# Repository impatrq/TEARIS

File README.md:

# TEARIS 🚀

**Auriculares con cancelación selectiva de ruido para personas con TEA y sensibilidad auditiva**

---

## 🎯 Introducción

TEARIS (TEA + auris, latín: oído) es un sistema innovador de auriculares con **cancelación activa de ruido adaptativa**, creado para personas con Trastorno del Espectro Autista (TEA), PTSD, fibromialgia, migrañas crónicas y otras condiciones con hipersensibilidad auditiva. El dispositivo filtra sonidos estridentes y molestos, mientras preserva voces humanas, alarmas y otros sonidos críticos, mejorando significativamente la calidad de vida y facilitando la inclusión educativa y social.

---

## 🛠️ Características destacadas

- **Cancelación inteligente de ruido** gracias a un modelo de Machine Learning embebido (TensorFlow Lite).
- **Microcontrolador Raspberry Pi Zero 2 W** y kernel RT-Linux para procesamiento en tiempo real (< 20 ms).
- **Algoritmo FxLMS** para generación de onda inversa y atenuación precisa.
- **Modos configurables (“Aula”, “Transporte”, etc.)** mediante app móvil.
- **Micrófonos INMP441 direccionales**, módulo Bluetooth CSR4.0 y tarjeta de sonido USB.
- **Diseño ergonómico y liviano** con carcasa impresa en 3D.
- **Autonomía de hasta 6 horas** con batería recargable de 2.000 mAh.
- **App móvil para personalización de filtros y perfiles**, en desarrollo.

---

## 🧩 Beneficios e impacto

- 🔹 **Reducción de estrés y crisis sensoriales**, favoreciendo la concentración.
- 🔹 **Inclusión escolar**, permitiendo a estudiantes con TEA rendir mejor en entornos ruidosos.
- 🔹 **Autonomía en espacios públicos** como transporte, comercios y hospitales.
- 🔹 **Escalable y accesible**, con costo estimado de USD 150 y posibilidad de colaboración con ONGs, escuelas y salud pública.

---

## 🧠 Arquitectura del sistema

```text
[ Micrófonos ➝ Raspberry Pi Zero W (ANC+ML) ➝ Auriculares ]
       ⬆⬇          ⬆                  ⬇
     Sonido       Procesamiento       Onda inversa
                    + App móvil
````

* Captura: micrófonos INMP441.
* Procesado: Raspberry Pi + TensorFlow Lite + FxLMS.
* Control: kernel de tiempo real.
* Reproducción: auriculares + Bluetooth.
* Energía: batería y gestión integrada.

---

## 🧪 Instalación y uso (prototipo)

```bash
git clone https://github.com/tu-usuario/tearis.git
cd tearis

# (Ejemplos de instalación)
pip install -r requirements.txt
# Compilación de firmware y carga en la Raspberry Pi
# Configuración de RT-Linux + deploy de modelos ML
```

Próximamente: **versión alfa de app móvil**, enlaces de descarga y documentación detallada.

---

## 👥 Equipo

Desarrollado en el Taller Regional Quilmes – E.E.T. Nº 7, Especialidad Aviónica:

* Tomás M. Bianco
* Luis Britez
* Santino R. Ramírez Tolosa
* Juan C. Somoza 

---

## 💰 Costos estimados

| Componente            |           Precio aprox. USD |
| --------------------- | --------------------------: |
| Micrófonos INMP441    |                          20 |
| Raspberry Pi Zero 2 W |                          20 |
| Carcasa + soportes    |                          15 |
| Tarjeta de audio USB  |                          15 |
| Bluetooth CSR 4.0     |                          15 |
| Batería 2.000 mAh     |                          12 |
| Cables y conectores   |                           5 |
| **Total estimado**    | **150 USD** (\~ARS 183.000) |

Financiado mediante cooperadora escolar, equipo propio y sponsors.

---

## 🛠️ Roadmap

1. Prototipo funcional y pruebas iniciales.
2. Ajuste de filtros y perfiles según feedback.
3. Lanzamiento de app móvil beta.
4. Validación con usuarios reales en escuelas.
5. Optimización energética y ergonomía.
6. Búsqueda de socios estratégicos (ONGs, salud, educación).

---

## 🎉 Contribuciones

¡Sumate! Tu ayuda puede incluir:

* Mejora y validación del ML.
* Diseño de carcasa y ergonomía.
* Desarrollo y testing de la app.
* Diseño, pruebas de hardware y PCB.

Consulta el archivo [CONTRIBUTING.md](CONTRIBUTING.md) para más detalles.

---

## 🔗 Referencias

* Autismo y sobrecarga sensorial (Ministerio de Salud Argentina)
* Estudios de misofonía y sensorialidad
* Soluciones similares en ANC adaptativo

---
---

**TEARIS no es solo tecnología, es inclusión.** 🚀

```

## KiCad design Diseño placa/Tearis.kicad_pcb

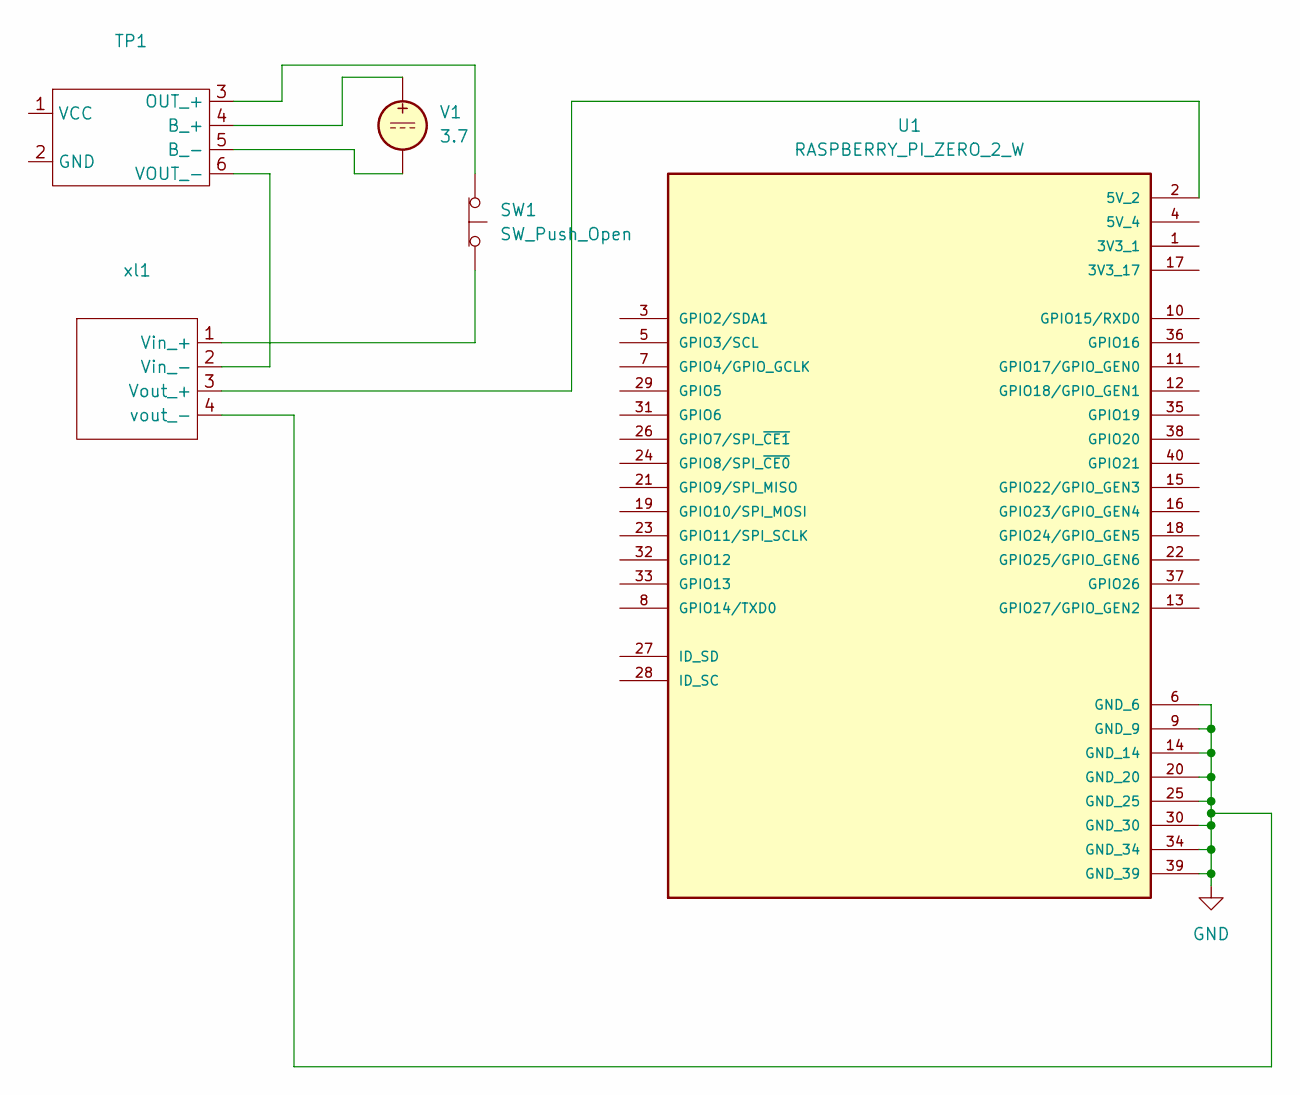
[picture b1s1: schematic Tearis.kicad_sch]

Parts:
SW1: SW_Push_Open; TestPoint_2Pads_Pitch5.08mm_Drill1.3mm
TP1: TP4056-18650
U1: RASPBERRY_PI_ZERO_2_W; Raspberry_Pi_Zero_Socketed_THT_FaceDown_MountingHoles; PARTREV April 2024
V1: 3.7; PinHeader_1x02_P2.54mm_Vertical
xl1: XL6009_module

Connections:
GND: U1.6 (GND), U1.9 (GND), U1.14 (GND), U1.20 (GND), U1.25 (GND), U1.30 (GND), U1.34 (GND), U1.39 (GND), xl1.4 (vout_-)
unnamed: SW1.1 (A), TP1.3 (OUT_+)
unnamed: SW1.2 (B), xl1.1 (Vin_+)
unnamed: TP1.4 (B_+), V1.1
unnamed: TP1.5 (B_-), V1.2
unnamed: TP1.6 (VOUT_-), xl1.2 (Vin_-)
unnamed: U1.2 (5V), xl1.3 (Vout_+)

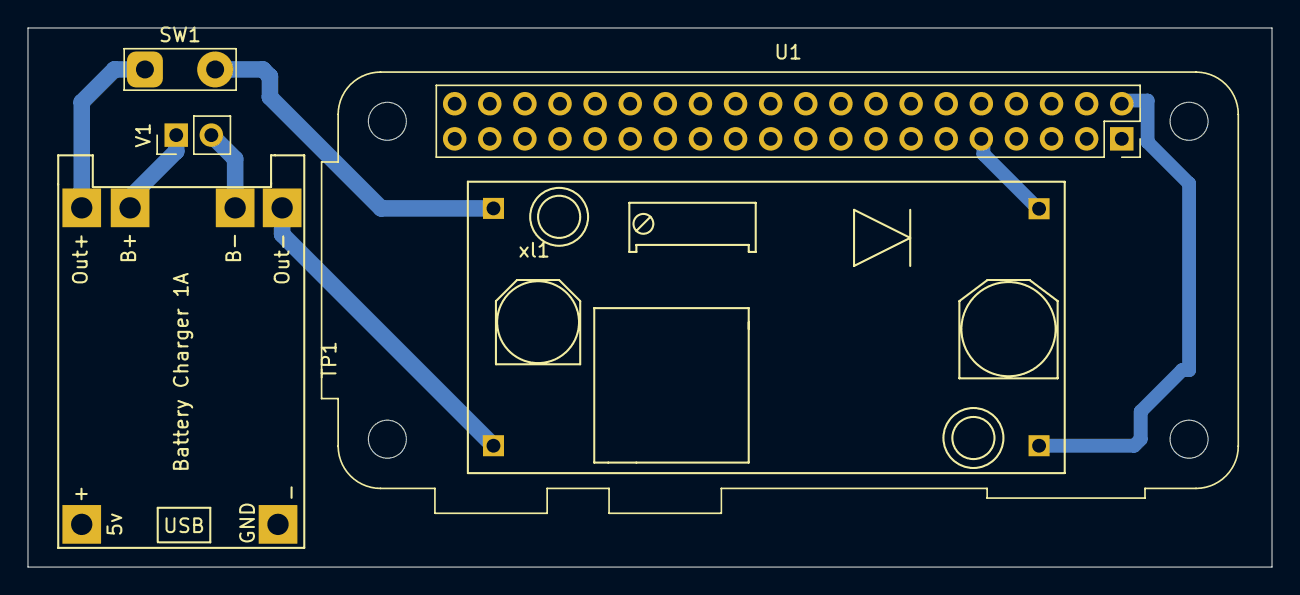
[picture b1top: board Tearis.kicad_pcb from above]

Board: 2 copper layers, 90.0 x 39.0 mm, 5 parts (0 on the bottom side), 7 nets.

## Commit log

2025-06-10 Rename app to app / firmware
2025-06-10 Create pagina web
2025-06-23 Rename pagina web to pagina web /httlm
2025-06-23 Create docs
2025-06-23 Rename docs to docs /README
2025-06-23 Rename README.md to docs/README.md
2025-06-23 Create lista_de_componentes
2025-06-23 Create modelado_3D
2025-06-23 Create carpeta_de_campo
2025-06-23 Create esquematico
2025-06-23 Create #
2025-06-23 Create pipi
2025-06-23 Create Rasberry_pi_zero_w
2025-06-23 Create datasheet
2025-06-24 Create FILE
2025-06-25 Agregar sitio web
2025-06-25 Create Pagina
2025-07-12 Rename firmware to firmware
2025-07-12 Rename firmware to firmware
2025-07-13 Agrego IA inicial
2025-07-13 interfaz app
2025-07-14 Primer prototipo
2025-07-14 Cambios en App
2025-07-14 Actualizo web
2025-07-17 Carpeta de campo
2025-09-12 Filtro iir
2025-10-07 diseño placa
2025-10-09 actualización interfaz
2025-10-21 script para filtro
2025-10-22 Revise README for TEARIS Android app
    Updated README to reflect app features, installation, and usage instructions for TEARIS app.
2025-10-24 apk de la app
2025-10-27 actualizacion diseño
2025-10-28 actualización componentes
2025-10-30 actualización del 3d
2025-10-31 actualización placa
2025-10-31 Manual de usuario
2025-10-31 Actualizo manual de usuario
2025-11-03 actualización de la app
2025-11-05 cambios app
2025-11-06 Cancelacion de ruido en python
2025-11-07 modificación script
2025-11-13 permisos android
2025-11-13 actualización app
2025-11-14 Segundo prototipo
2025-11-14 Cuarto Prototipo
2025-11-14 mas progreso de mayo
2025-11-14 Quinto prototipo
2025-11-14 DIseño de tapa
2025-11-14 tapa
2025-11-14 Sexto prototipo
2025-11-14 saco
2025-11-14 progreso de junio
2025-11-14 progreso de julio
2025-11-14 progreso agosto
2025-11-14 version final BLE
2025-11-14 Progreso de septiembre
2025-11-14 mas progreso septiembre
